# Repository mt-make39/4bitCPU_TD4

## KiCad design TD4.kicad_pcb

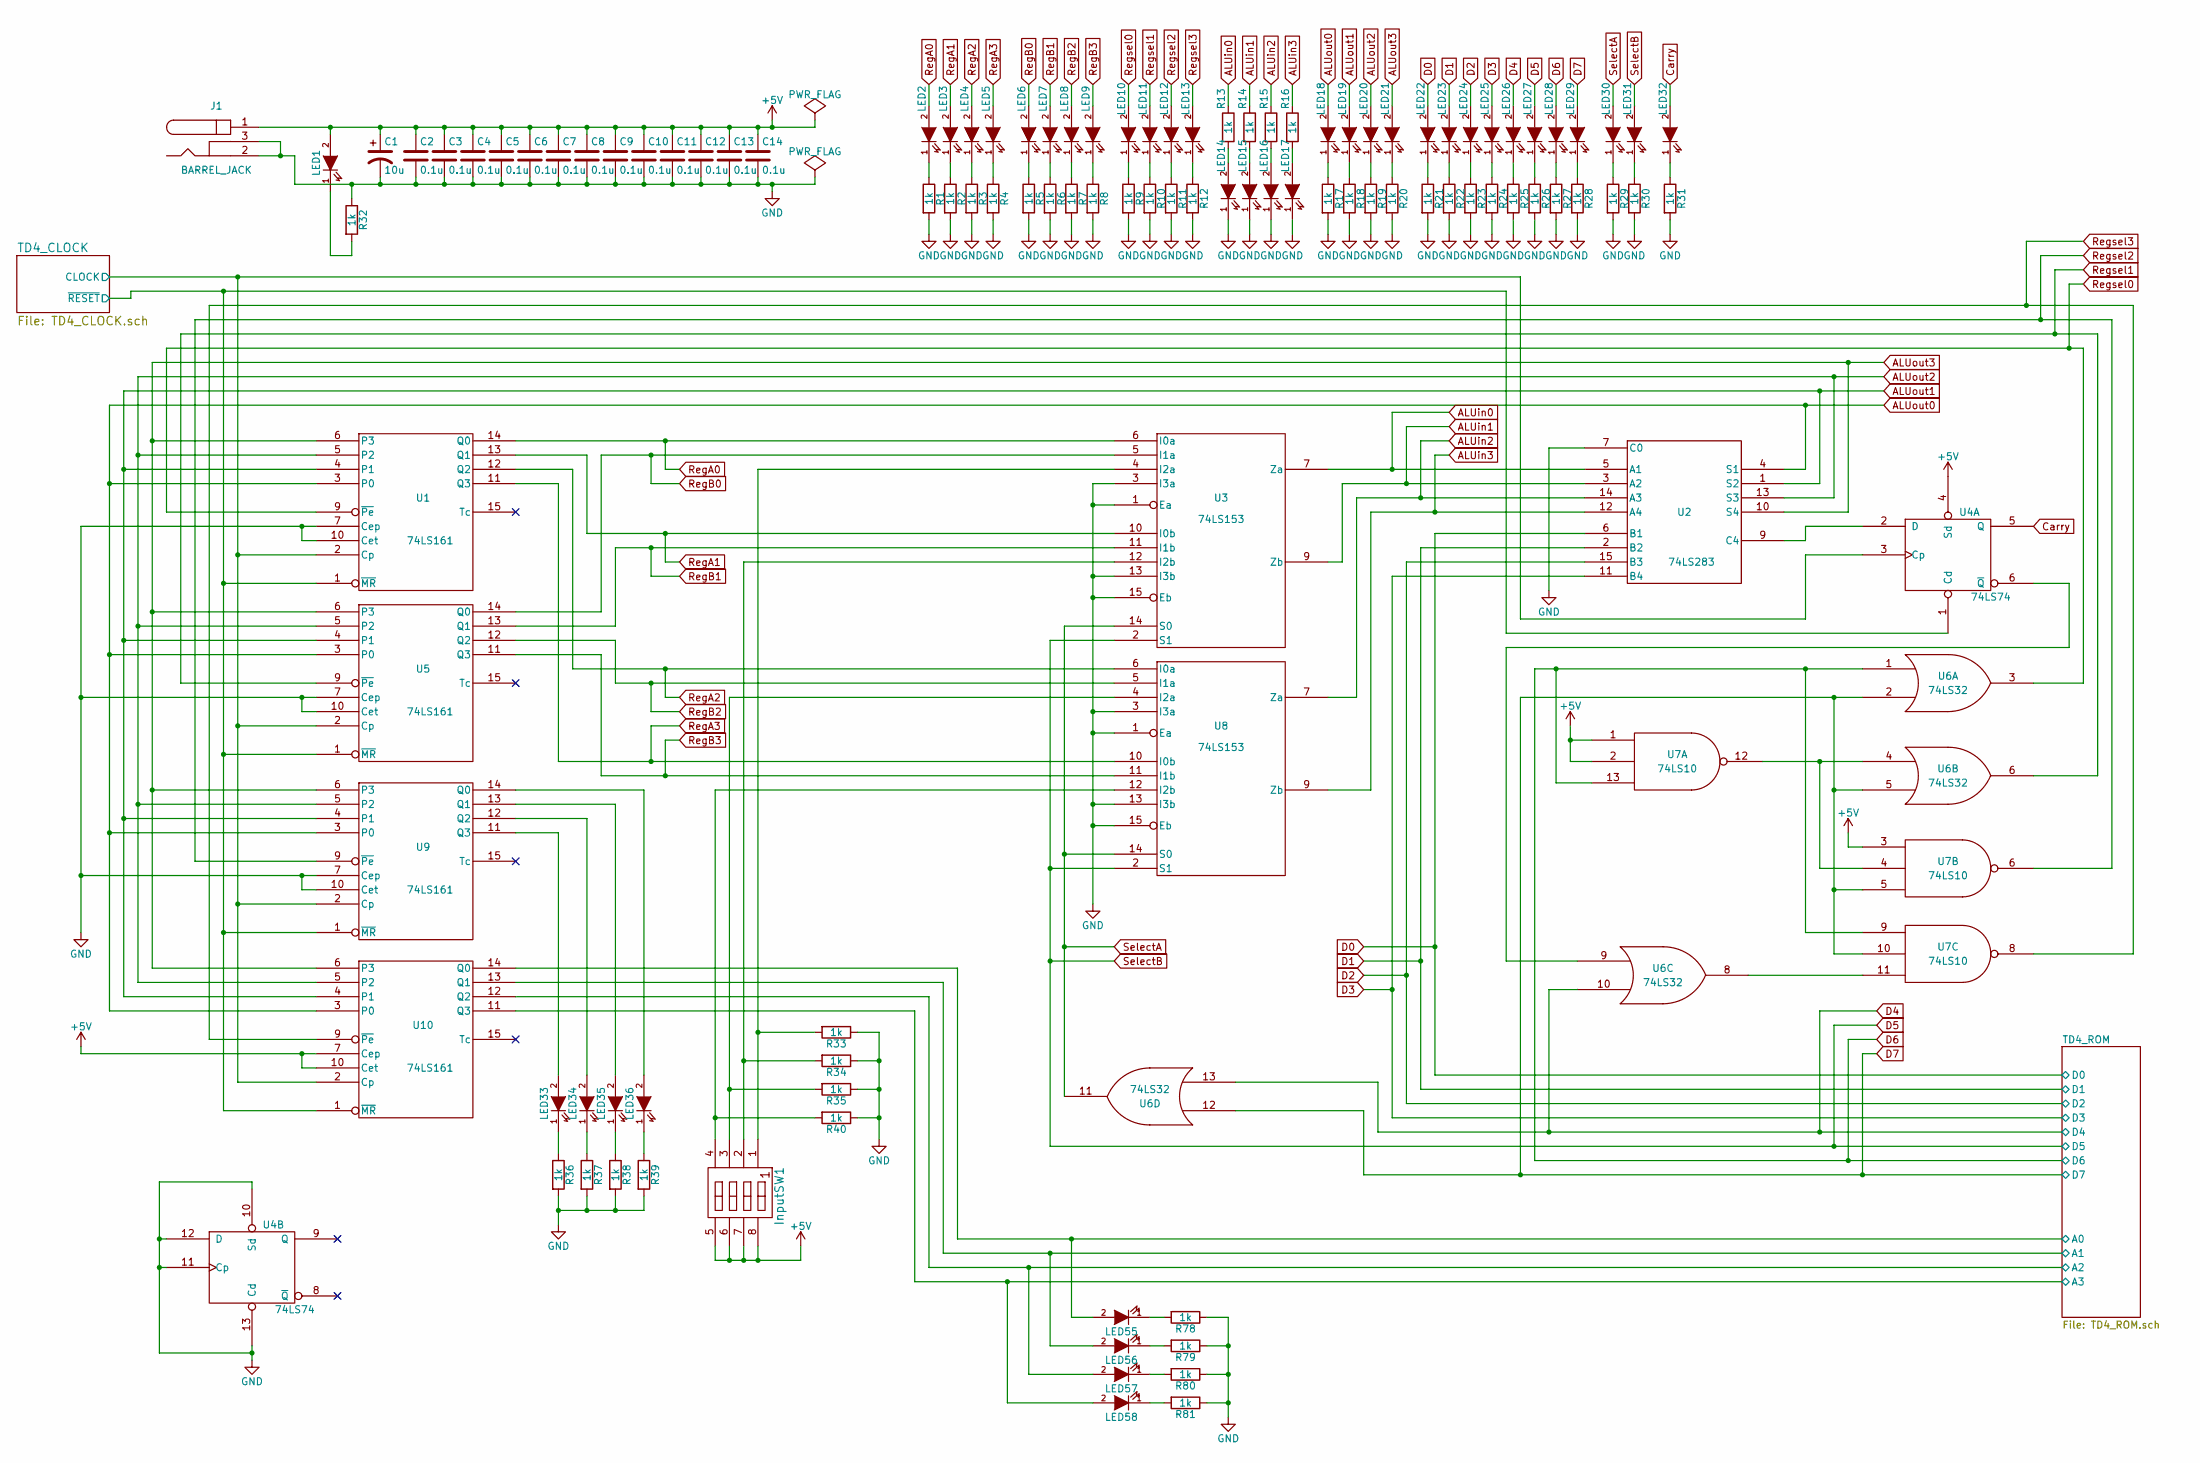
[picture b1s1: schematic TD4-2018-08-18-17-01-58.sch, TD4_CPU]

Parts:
C1: 10u; CP_Radial_D5.0mm_P2.00mm
C2, C3, C4, C5, C6, C7, C8, C9, C10, C11, C12, C13, C14: 0.1u; C_Rect_L4.0mm_W2.5mm_P2.50mm
InputSW1: DIP_SW4; SW_DIP_x4_W7.62mm_Slide
J1: BARREL_JACK
LED1: LED; LED_D5.0mm
LED2, LED3, LED4, LED5, LED6, LED7, LED8, LED9, LED10, LED11, LED12, LED13, LED14, LED15, LED16, LED17, LED18, LED19, LED20, LED21, LED22, LED23, LED24, LED25, LED26, LED27, LED28, LED29, LED30, LED31, LED32, LED33, LED34, LED35, LED36, LED55, LED56, LED57, LED58: LED; LED_D3.0mm
R1, R2, R3, R4, R5, R6, R7, R8, R9, R10, R11, R12, R13, R14, R15, R16, R17, R18, R19, R20, R21, R22, R23, R24, R25, R26, R27, R28, R29, R30, R31, R32, R33, R34, R35, R36, R37, R38, R39, R40, R78, R79, R80, R81: 1k; R4
U1, U5, U9, U10: 74LS161; DIP-16_W7.62mm
U2: 74LS283; DIP-16_W7.62mm
U3, U8: 74LS153; DIP-16_W7.62mm
U4: 74LS74; DIP-14_W7.62mm
U6: 74LS32; DIP-14_W7.62mm
U7: 74LS10; DIP-14_W7.62mm

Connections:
+5V: C1.1, C2.1, C3.1, C4.1, C5.1, C6.1, C7.1, C8.1, C9.1, C10.1, C11.1, C12.1, C13.1, C14.1, InputSW1.5, InputSW1.6, InputSW1.7, InputSW1.8, J1.1, LED1.2 (A), U1.16 (VCC), U2.16 (VCC), U3.16 (VCC), U4.4 (Sd), U4.14 (VCC), U5.16 (VCC), U6.14 (VCC), U7.1, U7.2, U7.3, U7.14 (VCC), U8.16 (VCC), U9.16 (VCC), U10.7 (Cep), U10.10 (Cet), U10.16 (VCC); also elsewhere on the board
/TD4_CLOCK/CLOCK: U1.2 (Cp), U4.3 (Cp), U5.2 (Cp), U9.2 (Cp), U10.2 (Cp); also elsewhere on the board
/TD4_CLOCK/~RESET: U1.1 (~MR), U4.1 (Cd), U5.1 (~MR), U9.1 (~MR), U10.1 (~MR); also elsewhere on the board
/TD4_ROM/A0: LED55.2 (A), U10.14 (Q0); also elsewhere on the board
/TD4_ROM/A1: LED56.2 (A), U10.13 (Q1); also elsewhere on the board
/TD4_ROM/A2: LED57.2 (A), U10.12 (Q2); also elsewhere on the board
/TD4_ROM/A3: LED58.2 (A), U10.11 (Q3); also elsewhere on the board
ALUin0: R13.1, U2.5 (A1), U3.7 (Za)
ALUin1: R14.1, U2.3 (A2), U3.9 (Zb)
ALUin2: R15.1, U2.14 (A3), U8.7 (Za)
ALUin3: R16.1, U2.12 (A4), U8.9 (Zb)
ALUout0: LED18.2 (A), U1.3 (P0), U2.4 (S1), U5.3 (P0), U9.3 (P0), U10.3 (P0)
ALUout1: LED19.2 (A), U1.4 (P1), U2.1 (S2), U5.4 (P1), U9.4 (P1), U10.4 (P1)
ALUout2: LED20.2 (A), U1.5 (P2), U2.13 (S3), U5.5 (P2), U9.5 (P2), U10.5 (P2)
ALUout3: LED21.2 (A), U1.6 (P3), U2.10 (S4), U5.6 (P3), U9.6 (P3), U10.6 (P3)
Carry: LED32.2 (A), U4.5 (Q)
D0: LED22.2 (A), U2.6 (B1); also elsewhere on the board
D1: LED23.2 (A), U2.2 (B2); also elsewhere on the board
D2: LED24.2 (A), U2.15 (B3); also elsewhere on the board
D3: LED25.2 (A), U2.11 (B4); also elsewhere on the board
D4: LED26.2 (A), U6.10, U6.13; also elsewhere on the board
D5: LED27.2 (A), LED31.2 (A), U3.2 (S1), U8.2 (S1); also elsewhere on the board
D6: LED28.2 (A), U6.1, U7.9, U7.13; also elsewhere on the board
D7: LED29.2 (A), U6.2, U6.5, U6.12, U7.5, U7.10; also elsewhere on the board
GND: C1.2, C2.2, C3.2, C4.2, C5.2, C6.2, C7.2, C8.2, C9.2, C10.2, C11.2, C12.2, C13.2, C14.2, J1.2, J1.3, LED14.1 (K), LED15.1 (K), LED16.1 (K), LED17.1 (K), R1.2, R2.2, R3.2, R4.2, R5.2, R6.2, R7.2, R8.2, R9.2, R10.2, R11.2, R12.2, R17.2, R18.2, R19.2, R20.2, R21.2, R22.2, R23.2, R24.2, R25.2, R26.2, R27.2, R28.2, R29.2, R30.2, R31.2, R32.1, R33.1, R34.1, R35.1, R36.2, R37.2, R38.2, R39.2, R40.1, R78.1, R79.1, R80.1, R81.1, U1.7 (Cep), U1.8 (GND), U1.10 (Cet), U2.7 (C0), U2.8 (GND), U3.1 (Ea), U3.3 (I3a), U3.8 (GND), U3.13 (I3b), U3.15 (Eb), U4.7 (GND), U4.10 (Sd), U4.11 (Cp), U4.12 (D), U4.13 (Cd), U5.7 (Cep), U5.8 (GND), U5.10 (Cet), U6.7 (GND), U7.7 (GND), U8.1 (Ea), U8.3 (I3a), U8.8 (GND), U8.13 (I3b), U8.15 (Eb), U9.7 (Cep), U9.8 (GND), U9.10 (Cet), U10.8 (GND); also elsewhere on the board
unnamed: InputSW1.1, R33.2, U3.4 (I2a)
unnamed: InputSW1.2, R34.2, U3.12 (I2b)
unnamed: InputSW1.3, R35.2, U8.4 (I2a)
unnamed: InputSW1.4, R40.2, U8.12 (I2b)
unnamed: LED1.1 (K), R32.2
unnamed: LED2.1 (K), R1.1
unnamed: LED3.1 (K), R2.1
unnamed: LED4.1 (K), R3.1
unnamed: LED5.1 (K), R4.1
unnamed: LED6.1 (K), R5.1
unnamed: LED7.1 (K), R6.1
unnamed: LED8.1 (K), R7.1
unnamed: LED9.1 (K), R8.1
unnamed: LED10.1 (K), R9.1
unnamed: LED11.1 (K), R10.1
unnamed: LED12.1 (K), R11.1
unnamed: LED13.1 (K), R12.1
unnamed: LED14.2 (A), R13.2
unnamed: LED15.2 (A), R14.2
unnamed: LED16.2 (A), R15.2
unnamed: LED17.2 (A), R16.2
unnamed: LED18.1 (K), R17.1
unnamed: LED19.1 (K), R18.1
unnamed: LED20.1 (K), R19.1
unnamed: LED21.1 (K), R20.1
unnamed: LED22.1 (K), R21.1
unnamed: LED23.1 (K), R22.1
unnamed: LED24.1 (K), R23.1
unnamed: LED25.1 (K), R24.1
unnamed: LED26.1 (K), R25.1
unnamed: LED27.1 (K), R26.1
unnamed: LED28.1 (K), R27.1
unnamed: LED29.1 (K), R28.1
unnamed: LED30.1 (K), R29.1
unnamed: LED31.1 (K), R30.1
unnamed: LED32.1 (K), R31.1
unnamed: LED33.1 (K), R36.1
unnamed: LED33.2 (A), U9.11 (Q3)
unnamed: LED34.1 (K), R37.1
unnamed: LED34.2 (A), U9.12 (Q2)
unnamed: LED35.1 (K), R38.1
unnamed: LED35.2 (A), U9.13 (Q1)
unnamed: LED36.1 (K), R39.1
unnamed: LED36.2 (A), U9.14 (Q0)
unnamed: LED55.1 (K), R78.2
unnamed: LED56.1 (K), R79.2
unnamed: LED57.1 (K), R80.2
unnamed: LED58.1 (K), R81.2
unnamed: U2.9 (C4), U4.2 (D)
unnamed: U4.6 (~Q), U6.9
unnamed: U6.4, U7.4, U7.12
unnamed: U6.8, U7.11
RegA0: LED2.2 (A), U1.14 (Q0), U3.6 (I0a)
RegA1: LED3.2 (A), U1.13 (Q1), U3.10 (I0b)
RegA2: LED4.2 (A), U1.12 (Q2), U8.6 (I0a)
RegA3: LED5.2 (A), U1.11 (Q3), U8.10 (I0b)
RegB0: LED6.2 (A), U3.5 (I1a), U5.14 (Q0)
RegB1: LED7.2 (A), U3.11 (I1b), U5.13 (Q1)
RegB2: LED8.2 (A), U5.12 (Q2), U8.5 (I1a)
RegB3: LED9.2 (A), U5.11 (Q3), U8.11 (I1b)
Regsel0: LED10.2 (A), U1.9 (~Pe), U6.3
Regsel1: LED11.2 (A), U5.9 (~Pe), U6.6
Regsel2: LED12.2 (A), U7.6, U9.9 (~Pe)
Regsel3: LED13.2 (A), U7.8, U10.9 (~Pe)
SelectA: LED30.2 (A), U3.14 (S0), U6.11, U8.14 (S0)

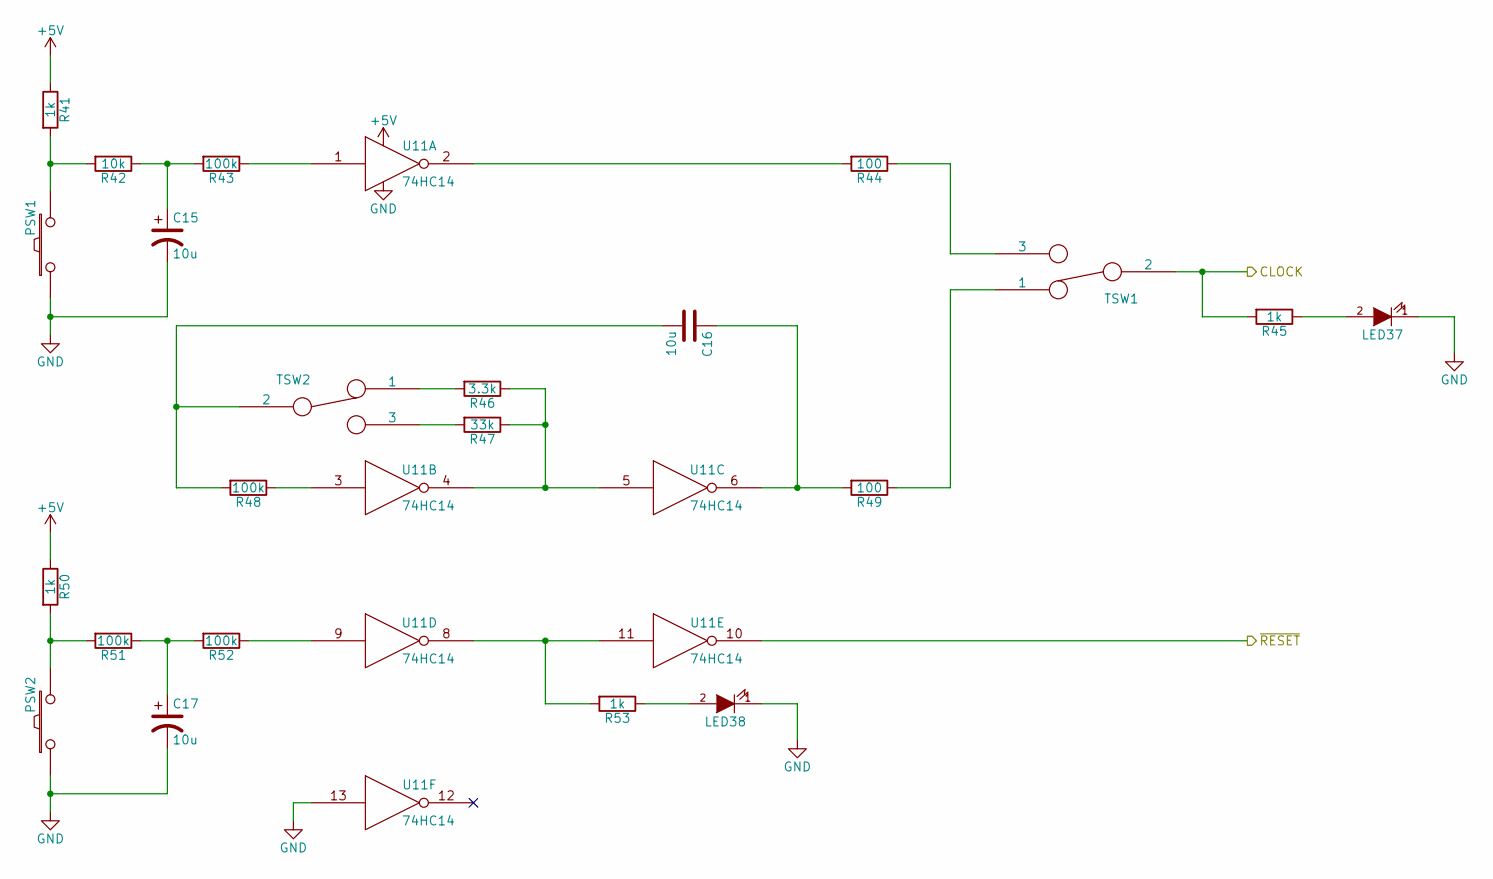
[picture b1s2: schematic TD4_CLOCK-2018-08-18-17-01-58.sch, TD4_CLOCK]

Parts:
C15, C17: 10u; CP_Radial_D4.0mm_P1.50mm
C16: 10u; CP_Radial_D5.0mm_P2.00mm
LED37, LED38: LED; LED_D5.0mm
PSW1, PSW2: SW_PUSH; SW_PUSH_6mm_h4.3mm
R41, R45, R50, R53: 1k; R4
R42: 10k; R4
R43, R48, R51, R52: 100k; R4
R44, R49: 100; R4
R46: 3.3k; R4
R47: 33k; R4
TSW1, TSW2: SWITCH_INV; Pin_Header_Straight_1x03_Pitch2.54mm
U11: 74HC14; DIP-14_W7.62mm

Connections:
+5V: R41.1, R50.1, U11.14 (VCC); also elsewhere on the board
/TD4_CLOCK/CLOCK: R45.2, TSW1.2; also elsewhere on the board
/TD4_CLOCK/~RESET: U11.10; also elsewhere on the board
GND: C15.2, C17.2, LED37.1 (K), LED38.1 (K), PSW1.1, PSW2.1, U11.7 (GND), U11.13; also elsewhere on the board
unnamed: C15.1, R42.1, R43.2
unnamed: C16.1, R49.2, U11.6
unnamed: C16.2, R48.2, TSW2.2
unnamed: C17.1, R51.1, R52.2
unnamed: LED37.2 (A), R45.1
unnamed: LED38.2 (A), R53.1
unnamed: PSW1.2, R41.2, R42.2
unnamed: PSW2.2, R50.2, R51.2
unnamed: R43.1, U11.1
unnamed: R44.1, TSW1.3
unnamed: R44.2, U11.2
unnamed: R46.1, R47.1, U11.4, U11.5
unnamed: R46.2, TSW2.1
unnamed: R47.2, TSW2.3
unnamed: R48.1, U11.3
unnamed: R49.1, TSW1.1
unnamed: R52.1, U11.9
unnamed: R53.2, U11.8, U11.11

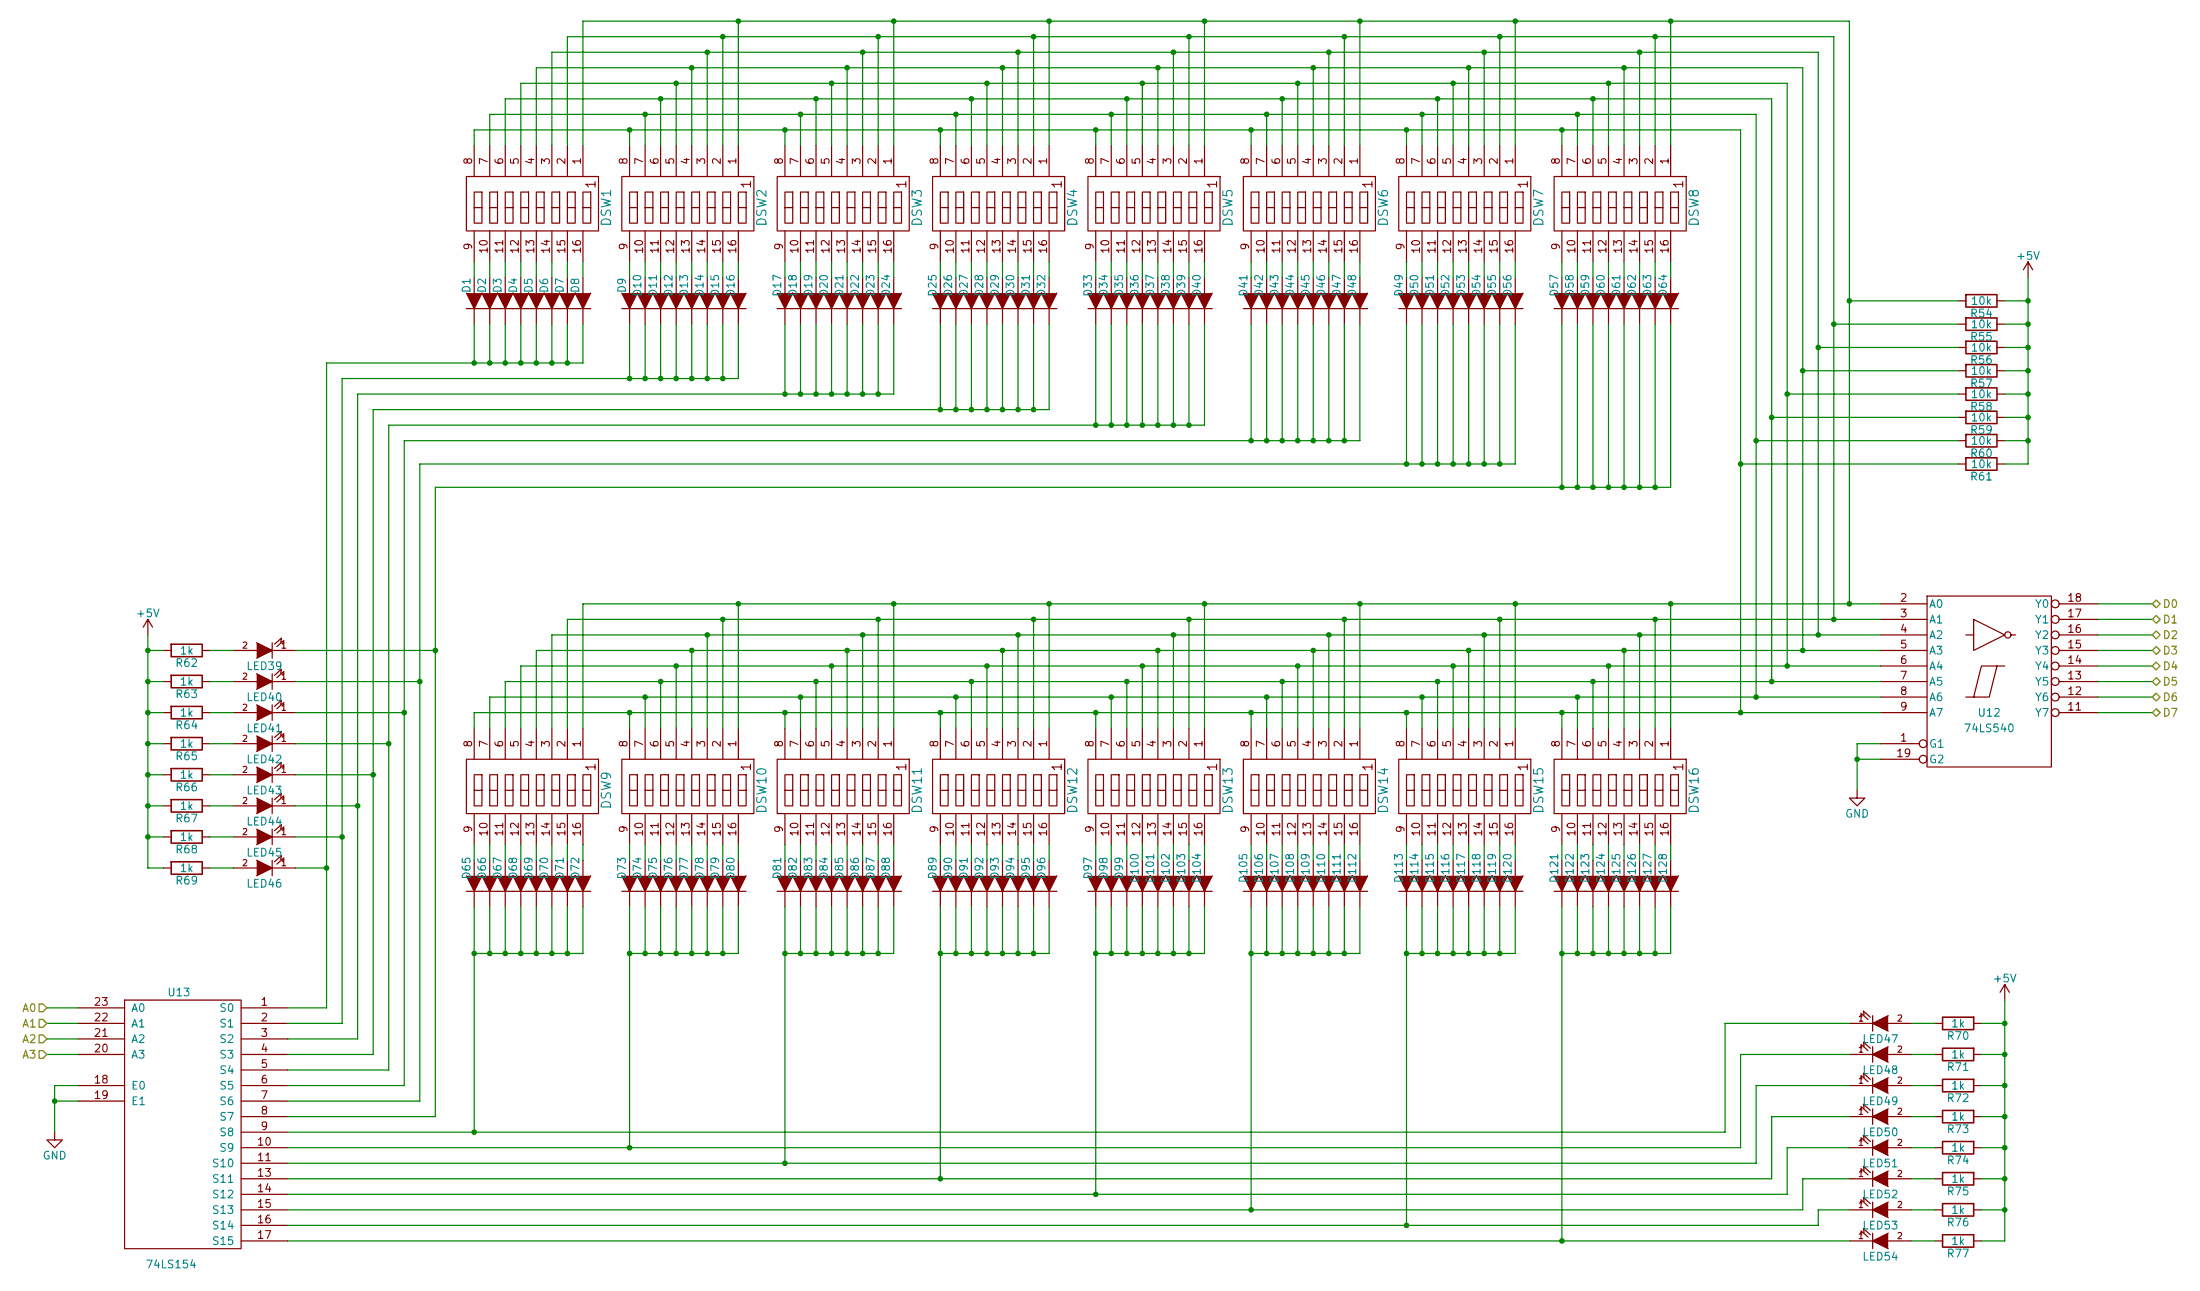
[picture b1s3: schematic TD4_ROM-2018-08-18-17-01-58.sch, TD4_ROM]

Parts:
D1, D2, D3, D4, D5, D6, D7, D8, D9, D10, D11, D12, D13, D14, D15, D16, D17, D18, D19, D20, D21, D22, D23, D24, D25, D26, D27, D28, D29, D30, D31, D32, D33, D34, D35, D36, D37, D38, D39, D40, D41, D42, D43, D44, D45, D46, D47, D48, D49, D50, D51, D52, D53, D54, D55, D56, D57, D58, D59, D60, D61, D62, D63, D64, D65, D66, D67, D68, D69, D70, D71, D72, D73, D74, D75, D76, D77, D78, D79, D80, D81, D82, D83, D84, D85, D86, D87, D88, D89, D90, D91, D92, D93, D94, D95, D96, D97, D98, D99, D100, D101, D102, D103, D104, D105, D106, D107, D108, D109, D110, D111, D112, D113, D114, D115, D116, D117, D118, D119, D120, D121, D122, D123, D124, D125, D126, D127, D128: D; 1S4
DSW1, DSW2, DSW3, DSW4, DSW5, DSW6, DSW7, DSW8, DSW9, DSW10, DSW11, DSW12, DSW13, DSW14, DSW15, DSW16: DIP_SW8; SW_DIP_x8_W7.62mm_Slide
LED39, LED40, LED41, LED42, LED43, LED44, LED45, LED46, LED47, LED48, LED49, LED50, LED51, LED52, LED53, LED54: LED; LED_D3.0mm
R54, R55, R56, R57, R58, R59, R60, R61: 10k; R4
R62, R63, R64, R65, R66, R67, R68, R69, R70, R71, R72, R73, R74, R75, R76, R77: 1k; R4
U12: 74LS540; DIP-20_W7.62mm
U13: 74LS154; DIP-24_W7.62mm

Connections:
+5V: R54.1, R55.1, R56.1, R57.1, R58.1, R59.1, R60.1, R61.1, R62.2, R63.2, R64.2, R65.2, R66.2, R67.2, R68.2, R69.2, R70.2, R71.2, R72.2, R73.2, R74.2, R75.2, R76.2, R77.2, U12.20 (VCC), U13.24 (VCC); also elsewhere on the board
/TD4_ROM/A0: U13.23 (A0); also elsewhere on the board
/TD4_ROM/A1: U13.22 (A1); also elsewhere on the board
/TD4_ROM/A2: U13.21 (A2); also elsewhere on the board
/TD4_ROM/A3: U13.20 (A3); also elsewhere on the board
D0: U12.18 (Y0); also elsewhere on the board
D1: U12.17 (Y1); also elsewhere on the board
D2: U12.16 (Y2); also elsewhere on the board
D3: U12.15 (Y3); also elsewhere on the board
D4: U12.14 (Y4); also elsewhere on the board
D5: U12.13 (Y5); also elsewhere on the board
D6: U12.12 (Y6); also elsewhere on the board
D7: U12.11 (Y7); also elsewhere on the board
GND: U12.1 (G1), U12.10 (GND), U12.19 (G2), U13.12 (GND), U13.18 (E0), U13.19 (E1); also elsewhere on the board
unnamed: D1.1 (K), D2.1 (K), D3.1 (K), D4.1 (K), D5.1 (K), D6.1 (K), D7.1 (K), D8.1 (K), LED46.1 (K), U13.1 (S0)
unnamed: D1.2 (A), DSW1.9
unnamed: D2.2 (A), DSW1.10
unnamed: D3.2 (A), DSW1.11
unnamed: D4.2 (A), DSW1.12
unnamed: D5.2 (A), DSW1.13
unnamed: D6.2 (A), DSW1.14
unnamed: D7.2 (A), DSW1.15
unnamed: D8.2 (A), DSW1.16
unnamed: D9.2 (A), DSW2.9
unnamed: D9.1 (K), D10.1 (K), D11.1 (K), D12.1 (K), D13.1 (K), D14.1 (K), D15.1 (K), D16.1 (K), LED45.1 (K), U13.2 (S1)
unnamed: D10.2 (A), DSW2.10
unnamed: D11.2 (A), DSW2.11
unnamed: D12.2 (A), DSW2.12
unnamed: D13.2 (A), DSW2.13
unnamed: D14.2 (A), DSW2.14
unnamed: D15.2 (A), DSW2.15
unnamed: D16.2 (A), DSW2.16
unnamed: D17.1 (K), D18.1 (K), D19.1 (K), D20.1 (K), D21.1 (K), D22.1 (K), D23.1 (K), D24.1 (K), LED44.1 (K), U13.3 (S2)
unnamed: D17.2 (A), DSW3.9
unnamed: D18.2 (A), DSW3.10
unnamed: D19.2 (A), DSW3.11
unnamed: D20.2 (A), DSW3.12
unnamed: D21.2 (A), DSW3.13
unnamed: D22.2 (A), DSW3.14
unnamed: D23.2 (A), DSW3.15
unnamed: D24.2 (A), DSW3.16
unnamed: D25.1 (K), D26.1 (K), D27.1 (K), D28.1 (K), D29.1 (K), D30.1 (K), D31.1 (K), D32.1 (K), LED43.1 (K), U13.4 (S3)
unnamed: D25.2 (A), DSW4.9
unnamed: D26.2 (A), DSW4.10
unnamed: D27.2 (A), DSW4.11
unnamed: D28.2 (A), DSW4.12
unnamed: D29.2 (A), DSW4.13
unnamed: D30.2 (A), DSW4.14
unnamed: D31.2 (A), DSW4.15
unnamed: D32.2 (A), DSW4.16
unnamed: D33.1 (K), D34.1 (K), D35.1 (K), D36.1 (K), D37.1 (K), D38.1 (K), D39.1 (K), D40.1 (K), LED42.1 (K), U13.5 (S4)
unnamed: D33.2 (A), DSW5.9
unnamed: D34.2 (A), DSW5.10
unnamed: D35.2 (A), DSW5.11
unnamed: D36.2 (A), DSW5.12
unnamed: D37.2 (A), DSW5.13
unnamed: D38.2 (A), DSW5.14
unnamed: D39.2 (A), DSW5.15
unnamed: D40.2 (A), DSW5.16
unnamed: D41.1 (K), D42.1 (K), D43.1 (K), D44.1 (K), D45.1 (K), D46.1 (K), D47.1 (K), D48.1 (K), LED41.1 (K), U13.6 (S5)
unnamed: D41.2 (A), DSW6.9
unnamed: D42.2 (A), DSW6.10
unnamed: D43.2 (A), DSW6.11
unnamed: D44.2 (A), DSW6.12
unnamed: D45.2 (A), DSW6.13
unnamed: D46.2 (A), DSW6.14
unnamed: D47.2 (A), DSW6.15
unnamed: D48.2 (A), DSW6.16
unnamed: D49.1 (K), D50.1 (K), D51.1 (K), D52.1 (K), D53.1 (K), D54.1 (K), D55.1 (K), D56.1 (K), LED40.1 (K), U13.7 (S6)
unnamed: D49.2 (A), DSW7.9
unnamed: D50.2 (A), DSW7.10
unnamed: D51.2 (A), DSW7.11
unnamed: D52.2 (A), DSW7.12
unnamed: D53.2 (A), DSW7.13
unnamed: D54.2 (A), DSW7.14
unnamed: D55.2 (A), DSW7.15
unnamed: D56.2 (A), DSW7.16
unnamed: D57.1 (K), D58.1 (K), D59.1 (K), D60.1 (K), D61.1 (K), D62.1 (K), D63.1 (K), D64.1 (K), LED39.1 (K), U13.8 (S7)
unnamed: D57.2 (A), DSW8.9
unnamed: D58.2 (A), DSW8.10
unnamed: D59.2 (A), DSW8.11
unnamed: D60.2 (A), DSW8.12
unnamed: D61.2 (A), DSW8.13
unnamed: D62.2 (A), DSW8.14
unnamed: D63.2 (A), DSW8.15
unnamed: D64.2 (A), DSW8.16
unnamed: D65.1 (K), D66.1 (K), D67.1 (K), D68.1 (K), D69.1 (K), D70.1 (K), D71.1 (K), D72.1 (K), LED47.1 (K), U13.9 (S8)
unnamed: D65.2 (A), DSW9.9
unnamed: D66.2 (A), DSW9.10
unnamed: D67.2 (A), DSW9.11
unnamed: D68.2 (A), DSW9.12
unnamed: D69.2 (A), DSW9.13
unnamed: D70.2 (A), DSW9.14
unnamed: D71.2 (A), DSW9.15
unnamed: D72.2 (A), DSW9.16
unnamed: D73.1 (K), D74.1 (K), D75.1 (K), D76.1 (K), D77.1 (K), D78.1 (K), D79.1 (K), D80.1 (K), LED48.1 (K), U13.10 (S9)
unnamed: D73.2 (A), DSW10.9
unnamed: D74.2 (A), DSW10.10
unnamed: D75.2 (A), DSW10.11
unnamed: D76.2 (A), DSW10.12
unnamed: D77.2 (A), DSW10.13
unnamed: D78.2 (A), DSW10.14
unnamed: D79.2 (A), DSW10.15
unnamed: D80.2 (A), DSW10.16
unnamed: D81.1 (K), D82.1 (K), D83.1 (K), D84.1 (K), D85.1 (K), D86.1 (K), D87.1 (K), D88.1 (K), LED49.1 (K), U13.11 (S10)
unnamed: D81.2 (A), DSW11.9
unnamed: D82.2 (A), DSW11.10
unnamed: D83.2 (A), DSW11.11
unnamed: D84.2 (A), DSW11.12
unnamed: D85.2 (A), DSW11.13
unnamed: D86.2 (A), DSW11.14
unnamed: D87.2 (A), DSW11.15
unnamed: D88.2 (A), DSW11.16
unnamed: D89.1 (K), D90.1 (K), D91.1 (K), D92.1 (K), D93.1 (K), D94.1 (K), D95.1 (K), D96.1 (K), LED50.1 (K), U13.13 (S11)
unnamed: D89.2 (A), DSW12.9
unnamed: D90.2 (A), DSW12.10
unnamed: D91.2 (A), DSW12.11
unnamed: D92.2 (A), DSW12.12
unnamed: D93.2 (A), DSW12.13
unnamed: D94.2 (A), DSW12.14
unnamed: D95.2 (A), DSW12.15
unnamed: D96.2 (A), DSW12.16
unnamed: D97.2 (A), DSW13.9
unnamed: D98.2 (A), DSW13.10
unnamed: D99.2 (A), DSW13.11
unnamed: D97.1 (K), D98.1 (K), D99.1 (K), D100.1 (K), D101.1 (K), D102.1 (K), D103.1 (K), D104.1 (K), LED51.1 (K), U13.14 (S12)
unnamed: D100.2 (A), DSW13.12
unnamed: D101.2 (A), DSW13.13
unnamed: D102.2 (A), DSW13.14
unnamed: D103.2 (A), DSW13.15
unnamed: D104.2 (A), DSW13.16
unnamed: D105.1 (K), D106.1 (K), D107.1 (K), D108.1 (K), D109.1 (K), D110.1 (K), D111.1 (K), D112.1 (K), LED52.1 (K), U13.15 (S13)
unnamed: D105.2 (A), DSW14.9
unnamed: D106.2 (A), DSW14.10
unnamed: D107.2 (A), DSW14.11
unnamed: D108.2 (A), DSW14.12
unnamed: D109.2 (A), DSW14.13
unnamed: D110.2 (A), DSW14.14
unnamed: D111.2 (A), DSW14.15
unnamed: D112.2 (A), DSW14.16
unnamed: D113.1 (K), D114.1 (K), D115.1 (K), D116.1 (K), D117.1 (K), D118.1 (K), D119.1 (K), D120.1 (K), LED53.1 (K), U13.16 (S14)
unnamed: D113.2 (A), DSW15.9
unnamed: D114.2 (A), DSW15.10
unnamed: D115.2 (A), DSW15.11
unnamed: D116.2 (A), DSW15.12
unnamed: D117.2 (A), DSW15.13
unnamed: D118.2 (A), DSW15.14
unnamed: D119.2 (A), DSW15.15
unnamed: D120.2 (A), DSW15.16
unnamed: D121.1 (K), D122.1 (K), D123.1 (K), D124.1 (K), D125.1 (K), D126.1 (K), D127.1 (K), D128.1 (K), LED54.1 (K), U13.17 (S15)
unnamed: D121.2 (A), DSW16.9
unnamed: D122.2 (A), DSW16.10
unnamed: D123.2 (A), DSW16.11
unnamed: D124.2 (A), DSW16.12
unnamed: D125.2 (A), DSW16.13
unnamed: D126.2 (A), DSW16.14
unnamed: D127.2 (A), DSW16.15
unnamed: D128.2 (A), DSW16.16
unnamed: DSW1.1, DSW2.1, DSW3.1, DSW4.1, DSW5.1, DSW6.1, DSW7.1, DSW8.1, DSW9.1, DSW10.1, DSW11.1, DSW12.1, DSW13.1, DSW14.1, DSW15.1, DSW16.1, R54.2, U12.2 (A0)
unnamed: DSW1.2, DSW2.2, DSW3.2, DSW4.2, DSW5.2, DSW6.2, DSW7.2, DSW8.2, DSW9.2, DSW10.2, DSW11.2, DSW12.2, DSW13.2, DSW14.2, DSW15.2, DSW16.2, R55.2, U12.3 (A1)
unnamed: DSW1.3, DSW2.3, DSW3.3, DSW4.3, DSW5.3, DSW6.3, DSW7.3, DSW8.3, DSW9.3, DSW10.3, DSW11.3, DSW12.3, DSW13.3, DSW14.3, DSW15.3, DSW16.3, R56.2, U12.4 (A2)
unnamed: DSW1.4, DSW2.4, DSW3.4, DSW4.4, DSW5.4, DSW6.4, DSW7.4, DSW8.4, DSW9.4, DSW10.4, DSW11.4, DSW12.4, DSW13.4, DSW14.4, DSW15.4, DSW16.4, R57.2, U12.5 (A3)
unnamed: DSW1.5, DSW2.5, DSW3.5, DSW4.5, DSW5.5, DSW6.5, DSW7.5, DSW8.5, DSW9.5, DSW10.5, DSW11.5, DSW12.5, DSW13.5, DSW14.5, DSW15.5, DSW16.5, R58.2, U12.6 (A4)
unnamed: DSW1.6, DSW2.6, DSW3.6, DSW4.6, DSW5.6, DSW6.6, DSW7.6, DSW8.6, DSW9.6, DSW10.6, DSW11.6, DSW12.6, DSW13.6, DSW14.6, DSW15.6, DSW16.6, R59.2, U12.7 (A5)
unnamed: DSW1.7, DSW2.7, DSW3.7, DSW4.7, DSW5.7, DSW6.7, DSW7.7, DSW8.7, DSW9.7, DSW10.7, DSW11.7, DSW12.7, DSW13.7, DSW14.7, DSW15.7, DSW16.7, R60.2, U12.8 (A6)
unnamed: DSW1.8, DSW2.8, DSW3.8, DSW4.8, DSW5.8, DSW6.8, DSW7.8, DSW8.8, DSW9.8, DSW10.8, DSW11.8, DSW12.8, DSW13.8, DSW14.8, DSW15.8, DSW16.8, R61.2, U12.9 (A7)
unnamed: LED39.2 (A), R62.1
unnamed: LED40.2 (A), R63.1
unnamed: LED41.2 (A), R64.1
unnamed: LED42.2 (A), R65.1
unnamed: LED43.2 (A), R66.1
unnamed: LED44.2 (A), R67.1
unnamed: LED45.2 (A), R68.1
unnamed: LED46.2 (A), R69.1
unnamed: LED47.2 (A), R70.1
unnamed: LED48.2 (A), R71.1
unnamed: LED49.2 (A), R72.1
unnamed: LED50.2 (A), R73.1
unnamed: LED51.2 (A), R74.1
unnamed: LED52.2 (A), R75.1
unnamed: LED53.2 (A), R76.1
unnamed: LED54.2 (A), R77.1

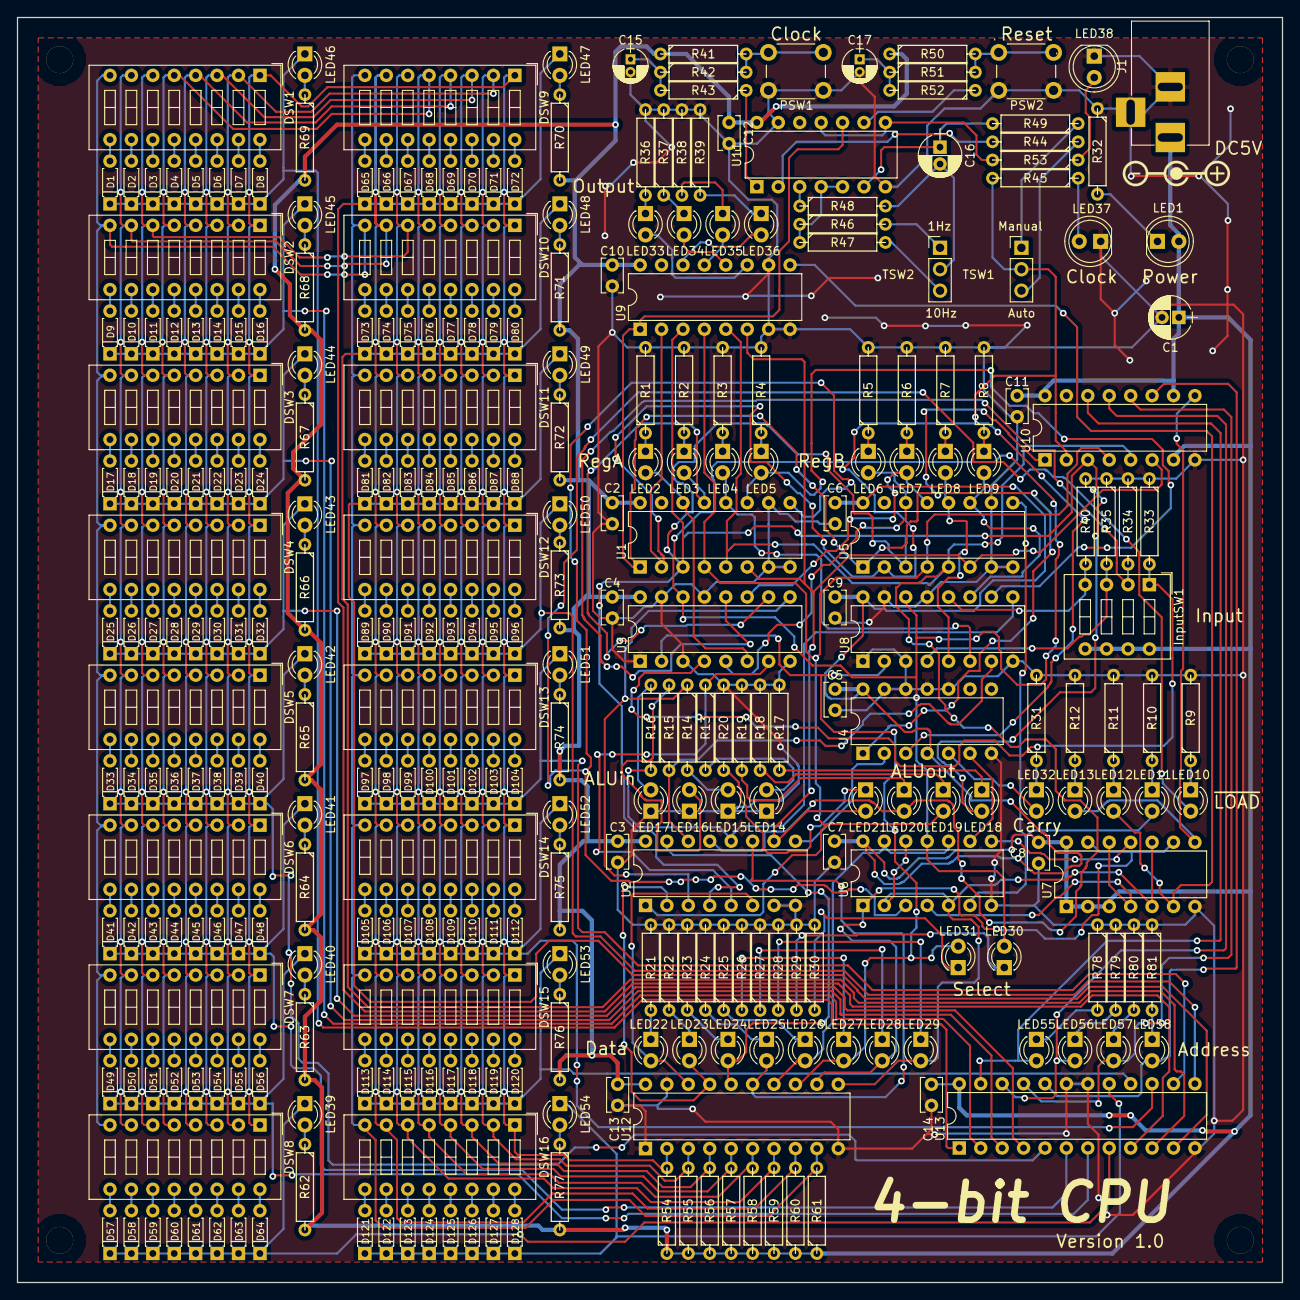
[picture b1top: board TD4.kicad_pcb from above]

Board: 2 copper layers, 150.0 x 150.0 mm, 319 parts (0 on the bottom side), 276 nets.

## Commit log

2019-01-29 Add New
